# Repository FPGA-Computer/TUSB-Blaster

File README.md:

The TUSB3410 USB stack was loosely based on Micah Dowty's polling based
USB driver, but was heavily modifed by me using TI's app notes and
source code examples. The resulting code is a mix of interrupt code and
polling. 

This is a clone of Altera USB Blaster based on the work of Kolja Waschk,
ixo.de. The code is ported to TI TUSB3410 USB to Serial converter chip
which is found in TI's MSP430 programmers and some very old cell phone
USB Serial interface dongles. 

TUSB3410 has a very slow microcontroller core. There are much better
chips out there. This is meant to serve as a demo of the USB stack and
to show that the chip can works as a USB JTAG device for OpenOCD and USB
Blaster clone in less than 3kB firmware.

TUSB3410 has onchip SRAM for firmware and you'll need to use my command
line util: load3410.exe to download its firmware.  Use libusb to make up a
.inf file/driver for it to stop window popup asking for drivers.

TI's apps loader util can also be used as an alternative.

License: Individual source files without copyright notices are written
by me and are distributed under GPL ver 2 or newer.

TUSB source code is compiled with SDCC 3.3.  I used Programmer's Notepad
as my IDE.  Win32 Util can be compileed with Pelles C for windows.

TUSB Blaster schematic/layout are Eagle CAD 6.5.0 files.

Project page: http://hw-by-design.blogspot.com/2018/08/tusb-blaster.html

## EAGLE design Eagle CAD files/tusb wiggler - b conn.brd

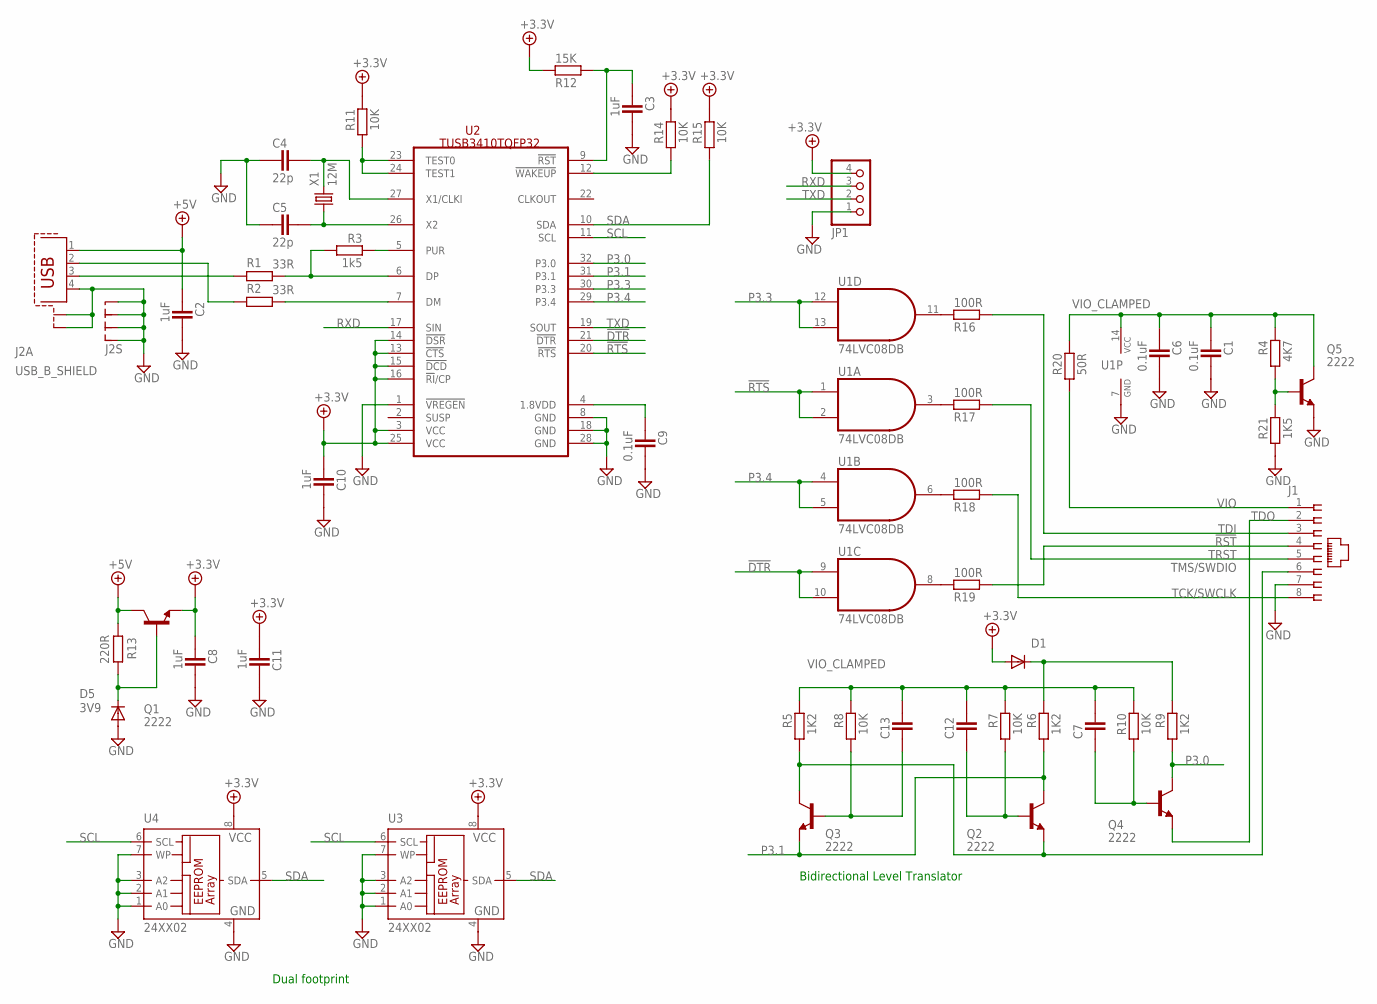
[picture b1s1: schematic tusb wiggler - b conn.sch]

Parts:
C1: 0.1uF; CAPC3215X168N
C2, C3, C8, C10, C11: 1uF; CAPC1608X92N
C4, C5: 22p; CAP2012X70N
C6: 0.1uF; CAPC1608X92N
C7, C12, C13: CAPACITOR_0805N; CAP2012X70N
C9: 0.1uF; CAP2012X70N
D1: DIODE-SOD110-W; SOD110-W
D5: 3V9; MELF-MLL41
J1: 520426-4
J2: USB_B_SHIELD; PN61729-S
JP1: PINHD-1X4_2.54; 1X04
Q1, Q2, Q3, Q4, Q5: 2222; SOT95P280X135-3N
R1, R2: 33R; RESC1608X55N
R3: 1k5; RESC1608X55N
R4: 4K7; RESC1608X55N
R5, R6, R9: 1K2; RESC1608X55N
R7, R8, R10, R11, R14, R15: 10K; RESC1608X55N
R12: 15K; RESC1608X55N
R13: 220R; RESC1608X55N
R16, R17, R18, R19: 100R; RESC3115X70N
R20: 50R; RESC1608X55N
R21: 1K5; RESC1608X55N
U1: 74LVC08DB; TSSOP14
U2: TUSB3410TQFP32; TQFP32-08
U3: 24XX02; TSSOP8
U4: 24XX02; SO-08
X1: 12M; HC49UP

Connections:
!DTR: U1.9 (I0), U1.10 (I1), U2.21 (!DTR)
!RST: J1.4, R19.2
!RTS: U1.1 (I0), U1.2 (I1), U2.20 (!RTS)
+3.3V: C8.1, C10.1, C11.1, D1.A, JP1.4, Q1.2 (E), R11.1, R12.1, R14.1, R15.1, U2.3 (VCC), U2.13 (!CTS), U2.14 (!DSR), U2.15 (!DCD), U2.16 (!RI!/CP), U2.25 (VCC), U3.8 (VCC), U4.8 (VCC)
+5V: C2.1, J2.1, Q1.3 (C), R13.1
GND: C1.2, C2.2, C3.2, C4.1, C5.1, C6.2, C8.2, C9.2, C10.2, C11.2, D5.A, J1.7, J2.4, J2.G1 (S1), J2.G2 (S1), J2.G3 (S2), J2.G4 (S2), J2.G5 (S3), J2.G6 (S4), JP1.1, Q5.2 (E), R21.2, U1.7 (GND), U2.1 (!VREGEN), U2.8 (GND), U2.18 (GND), U2.28 (GND), U3.1 (A0), U3.2 (A1), U3.3 (A2), U3.4 (GND), U3.7 (WP), U4.1 (A0), U4.2 (A1), U4.3 (A2), U4.4 (GND), U4.7 (WP)
unnamed: J2.3, R1.1
unnamed: C12.1, Q2.1 (B), R7.2
unnamed: C7.1, Q4.1 (B), R10.2
unnamed: C13.1, Q3.1 (B), R8.2
unnamed: R19.1, U1.8 (O)
unnamed: R11.2, U2.23 (TEST0), U2.24 (TEST1)
unnamed: C3.1, R12.2, U2.9 (!RST)
unnamed: R16.1, U1.11 (O)
unnamed: R17.1, U1.3 (O)
unnamed: R18.1, U1.6 (O)
unnamed: Q5.1 (B), R4.2, R21.1
unnamed: D1.C, R6.1, R9.1
unnamed: R14.2, U2.12 (!WAKEUP)
unnamed: J2.2, R2.1
unnamed: R1.2, R3.2, U2.6 (DP)
unnamed: R2.2, U2.7 (DM)
unnamed: D5.C, Q1.1 (B), R13.2
unnamed: C4.2, U2.27 (X1/CLKI), X1.2
unnamed: C5.2, U2.26 (X2), X1.1
unnamed: C9.1, U2.4 (1.8VDD)
unnamed: R3.1, U2.5 (PUR)
P3.0: Q4.3 (C), R9.2, U2.32 (P3.0)
P3.1: Q2.3 (C), Q3.2 (E), R6.2, U2.31 (P3.1)
P3.3: U1.12 (I0), U1.13 (I1), U2.30 (P3.3)
P3.4: U1.4 (I0), U1.5 (I1), U2.29 (P3.4)
RXD: JP1.3, U2.17 (SIN)
SCL: U2.11 (SCL), U3.6 (SCL), U4.6 (SCL)
SDA: R15.2, U2.10 (SDA), U3.5 (SDA), U4.5 (SDA)
TCK/SWCLK: J1.8, R18.2
TDI: J1.3, R16.2
TDO: J1.2, Q4.2 (E)
TMS/SWDIO: J1.6, Q2.2 (E), Q3.3 (C), R5.2
TRST: J1.5, R17.2
TXD: JP1.2, U2.19 (SOUT)
VIO: J1.1, R20.2
VIO_CLAMPED: C1.1, C6.1, C7.2, C12.2, C13.2, Q5.3 (C), R4.1, R5.1, R7.1, R8.1, R10.1, R20.1, U1.14 (VCC)

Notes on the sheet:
Bidirectional Level Translator
Dual footprint

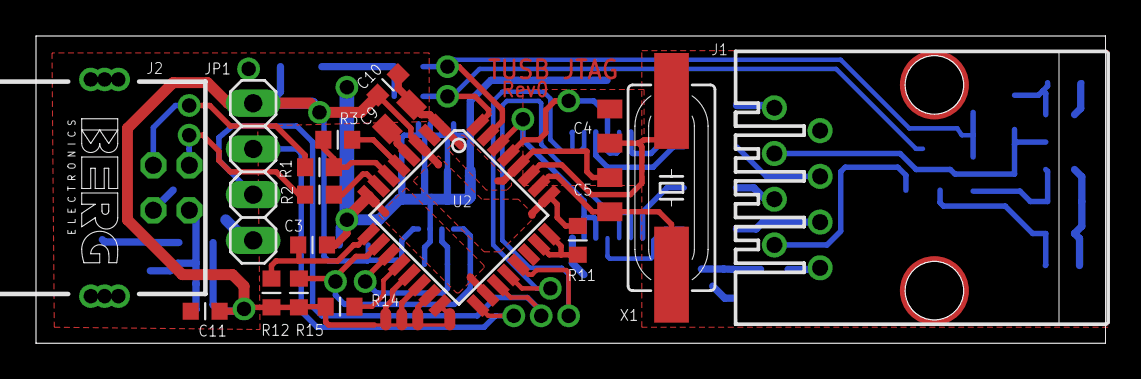
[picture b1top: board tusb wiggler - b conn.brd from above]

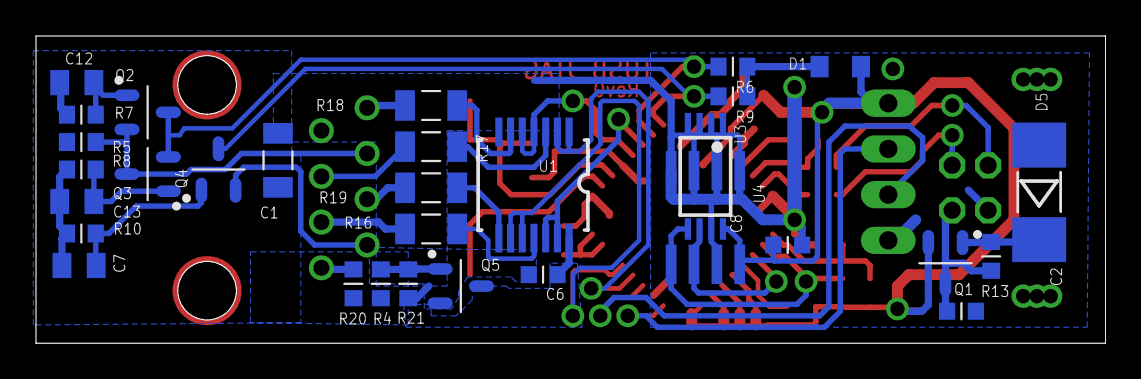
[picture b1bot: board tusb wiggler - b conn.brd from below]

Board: 2 copper layers, 59.4 x 17.1 mm, 49 parts (31 on the bottom side), 42 nets.

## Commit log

2014-08-07 TUBS Blaster initial commit
2018-08-07 Update project hosting
